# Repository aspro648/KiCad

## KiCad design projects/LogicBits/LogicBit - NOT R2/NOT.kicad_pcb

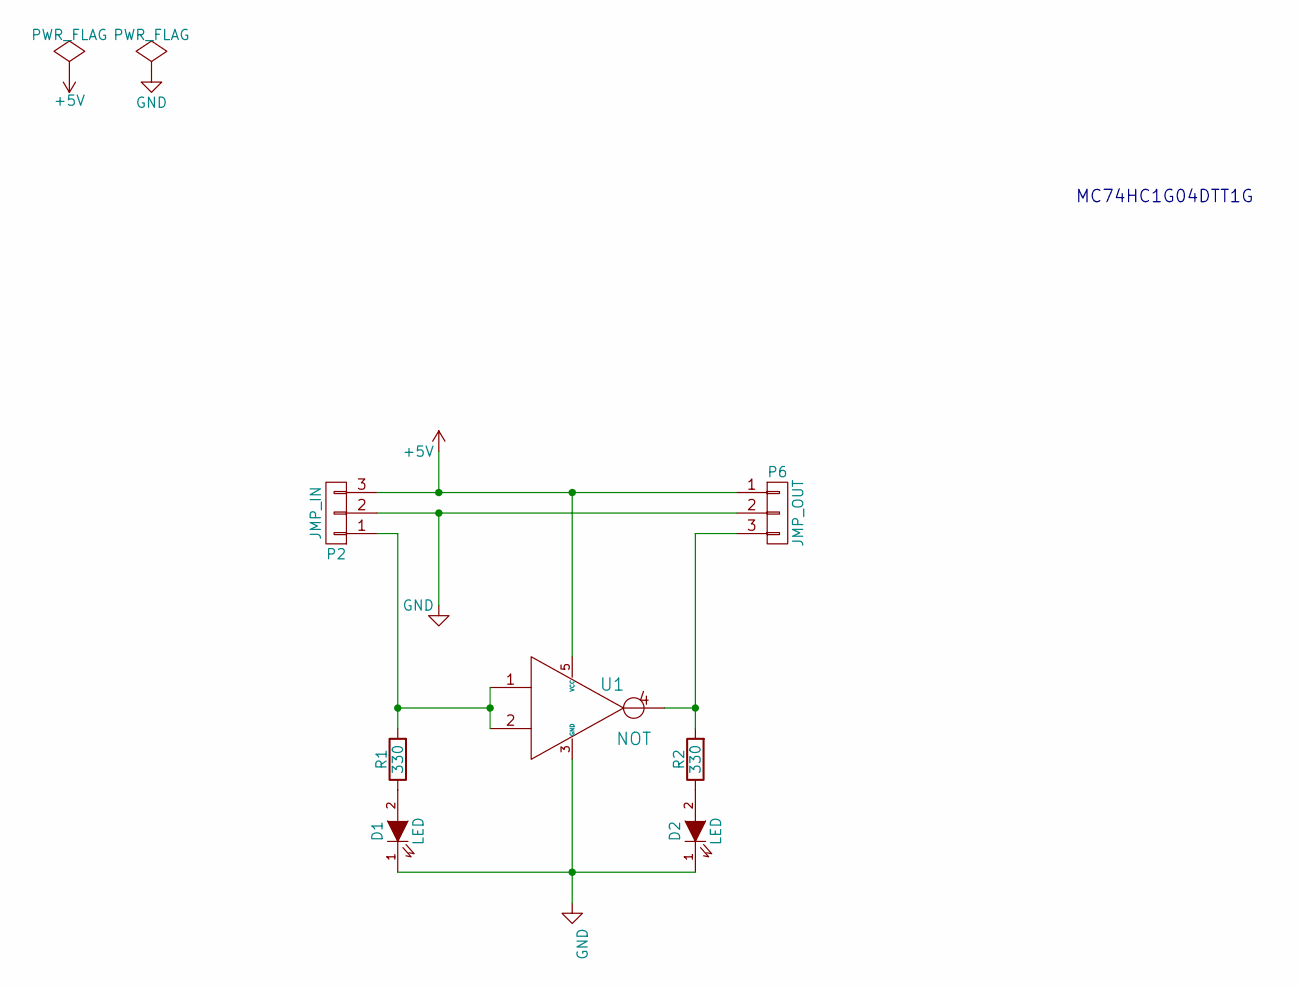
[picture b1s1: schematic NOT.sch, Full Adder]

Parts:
D1, D2: LED; LED-1206
P2: JMP_IN; Pin_Header_Angled_1x03
P6: JMP_OUT; Pin_Header_Angled_1x03
R1, R2: 330; R_1206
U1: NOT; SOT-23-5

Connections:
+5V: P2.3, P6.1, U1.5 (VCC)
GND: D1.1 (K), D2.1 (K), P2.2, P6.2, U1.3 (GND)
unnamed: D1.2 (A), R1.1
unnamed: D2.2 (A), R2.1
unnamed: P2.1, R1.2, U1.1, U1.2
unnamed: P6.3, R2.2, U1.4

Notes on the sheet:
MC74HC1G04DTT1G

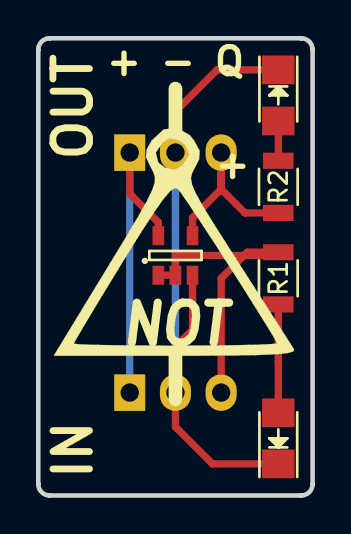
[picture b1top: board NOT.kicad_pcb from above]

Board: 2 copper layers, 15.2 x 25.4 mm, 9 parts (0 on the bottom side), 6 nets.

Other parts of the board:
Rec: myRec
VAL: MadeInOregonRev25

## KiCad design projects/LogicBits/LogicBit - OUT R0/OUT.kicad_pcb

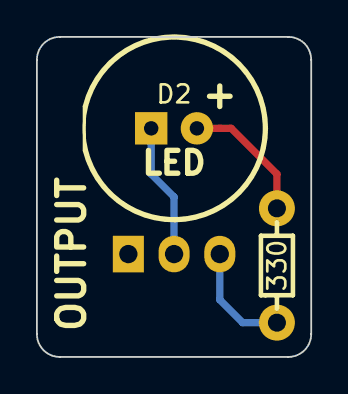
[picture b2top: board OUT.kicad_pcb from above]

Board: 2 copper layers, 15.2 x 17.8 mm, 4 parts (0 on the bottom side), 3 nets.

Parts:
D2: LED; LED-10MM
P2: JMP_IN; Pin_Header_Angled_1x03
R2: 330; Resistor_Horz
VAL: MadeInOregonRev25

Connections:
GND: D2.1, P2.2
unnamed: D2.2, R2.1
unnamed: P2.1, R2.2

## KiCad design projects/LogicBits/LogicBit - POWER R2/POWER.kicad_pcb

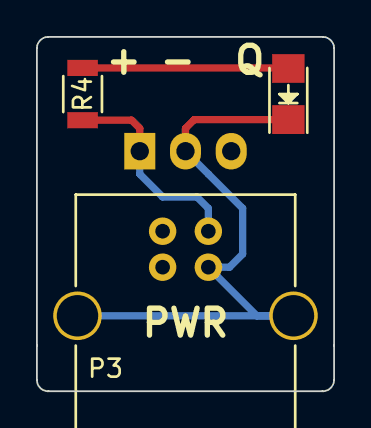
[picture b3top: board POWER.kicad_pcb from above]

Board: 2 copper layers, 16.5 x 19.7 mm, 5 parts (0 on the bottom side), 3 nets.

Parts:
D1: LED; LED-1206
P3: USB_B
P6: JMP_OUT; Pin_Header_Angled_1x03
R4: 330; R_1206
VAL: MadeInOregonRev25

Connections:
+5V: P3.1, P6.1, R4.1
GND: D1.1, P3.4, P3.5, P6.2
unnamed: D1.2, R4.2

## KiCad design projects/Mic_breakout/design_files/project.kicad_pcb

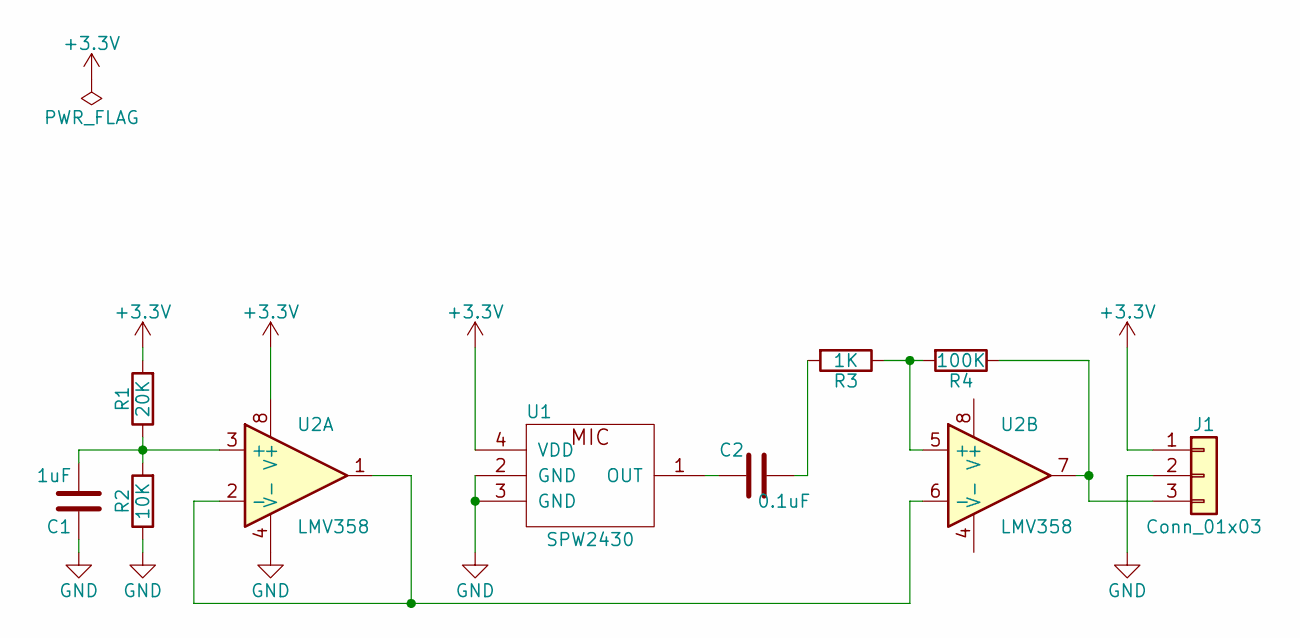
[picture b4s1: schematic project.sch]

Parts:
C1: 1uF; C_0805
C2: 0.1uF; C_0603
J1: Conn_01x03; Pin_Header_Straight_1x03_Pitch2.54mm
R1: 20K; R_0603
R2: 10K; R_0603
R3: 1K; R_0603
R4: 100K; R_0603
U1: SPW2430
U2: LMV358; TSSOP-8_3x3mm_Pitch0.65mm

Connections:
+3V3: J1.1, R1.2, U1.4 (VDD), U2.8 (V+)
GND: C1.1, J1.2, R2.1, U1.2 (GND), U1.3 (GND), U2.4 (V-)
unnamed: C1.2, R1.1, R2.2, U2.3 (+)
unnamed: C2.1, R3.2
unnamed: C2.2, U1.1 (OUT)
unnamed: J1.3, R4.1, U2.7
unnamed: R3.1, R4.2, U2.5 (+)
unnamed: U2.1, U2.2 (-), U2.6 (-)

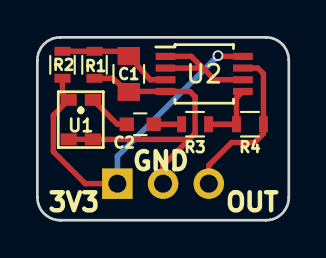
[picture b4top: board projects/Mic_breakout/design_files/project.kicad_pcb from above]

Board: 2 copper layers, 14.0 x 10.2 mm, 9 parts (0 on the bottom side), 8 nets.

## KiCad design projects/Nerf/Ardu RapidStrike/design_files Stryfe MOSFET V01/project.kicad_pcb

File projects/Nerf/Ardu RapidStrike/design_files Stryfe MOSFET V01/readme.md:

ArduStryfe MOSFET

Main Board
----------------
- 1 ea., 1N4001 1A Gen Purpose diode, https://www.digikey.com/short/p9ffm9
- 1 ea., MOSFET N-CH 30V 62A TO-220AB, Infineon IRLB8721PBF, https://www.digikey.com/short/p4fhcm
- 1 ea., PTC RESET FUSE 16V 900MA RADIAL, Littlefuse RUSBF090-2, https://www.digikey.com/short/p5vbvt
- 1 ea., PTC RESET FUSE 16V 2.5A RADIAL, Littlefuse RGEF250, https://www.digikey.com/short/pbfb9c

AA   3.5A @ 2.5s: RUSBF110 https://www.digikey.com/short/p5v5mz
LiPo 6.5A @ 2s:   RUSBF135 https://www.digikey.com/short/p5v5mc
MTRS  30A @ 3s: RGEF900  https://www.digikey.com/short/p5v54j

2.5A @ 2s: AHEF050: https://www.digikey.com/short/prwn0r
3.5A @ 2s: AHEF070: https://www.digikey.com/short/prwnv9

- 1 ea., 10K Resistors, 1/8W 5% generic, https://www.digikey.com/short/p4frj2 
- 1 ea., 2POS Picoblade vertical header, https://www.digikey.com/short/p9twrj
- 1 ea., 2POS PicoBlade housing, https://www.digikey.com/short/p4wz0d

- 2 ea., 12" PRE-CRIMP 1852 BLACK, https://www.digikey.com/short/pbfbnd

Revisions
----------------

License
----------------
[Attribution-ShareAlike 3.0 United States (CC BY-SA 3.0 US)](https://creativecommons.org/licenses/by-sa/3.0/us/)

You are free to:

- Share — copy and redistribute the material in any medium or format
- Adapt — remix, transform, and build upon the material

Under the following terms:

- Attribution — You must give appropriate credit, provide a link to the license, and indicate if changes were made. You may do so in any reasonable manner, but not in any way that suggests the licensor endorses you or your use.
- ShareAlike — If you remix, transform, or build upon the material, you must distribute your contributions under the same license as the original.

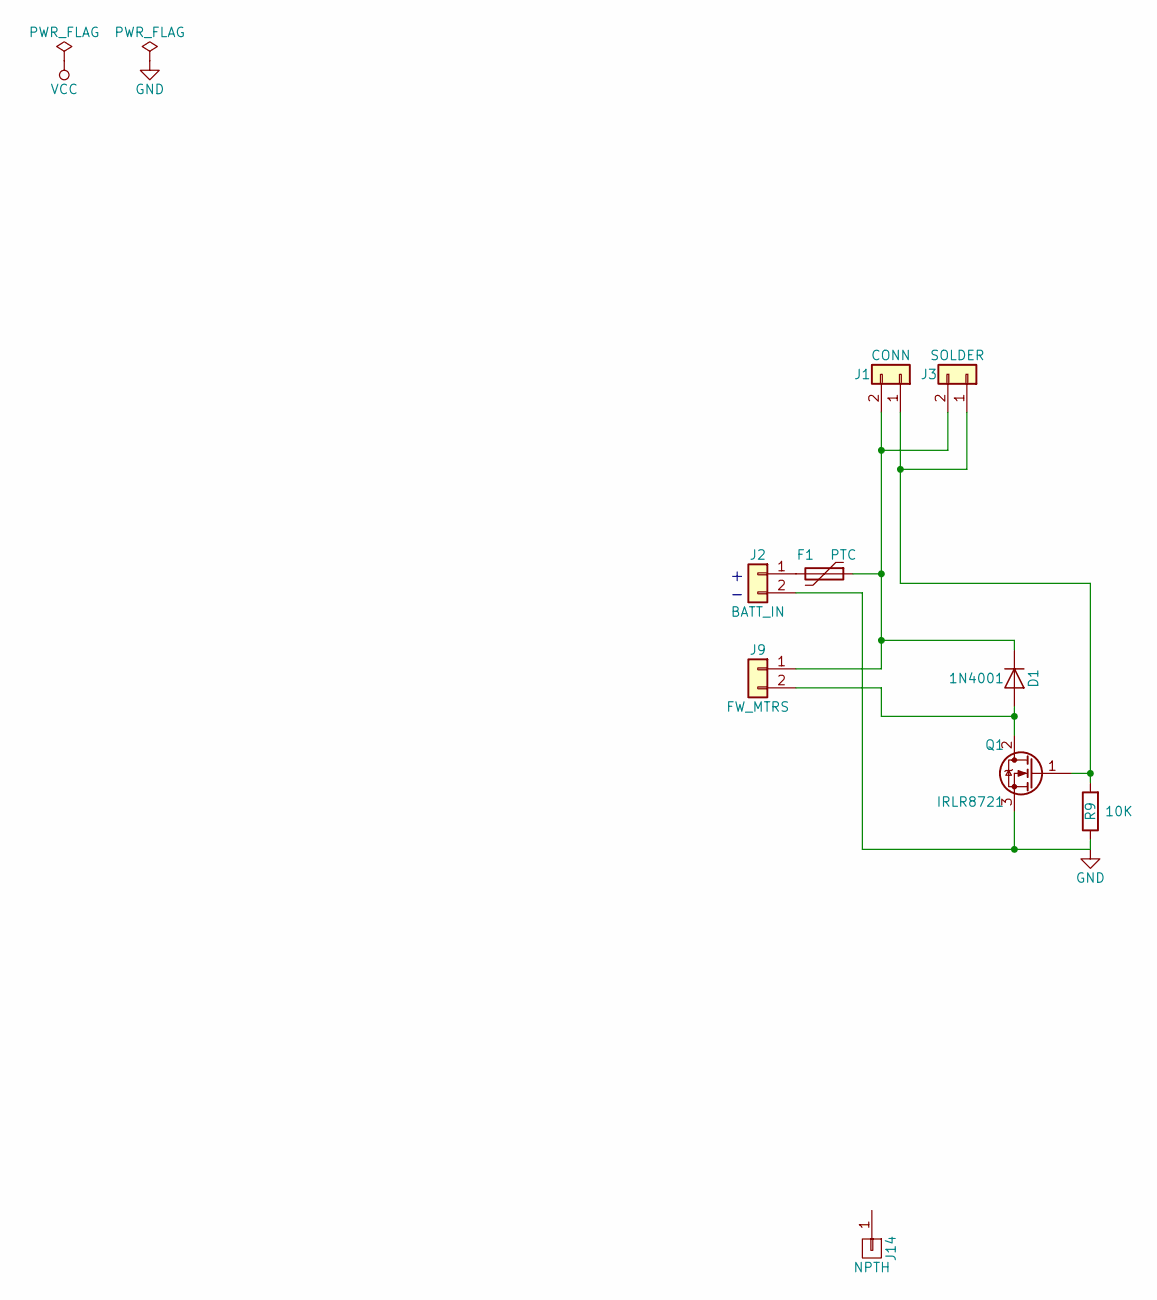
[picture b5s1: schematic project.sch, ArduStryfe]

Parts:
D1: 1N4001; D_DO-41
F1: PTC; Fuse_Littelfuse-LVR125
J1: CONN; Molex_PicoBlade_53047-0210_02x1.25mm_Straight
J2: BATT_IN; TerminalBlock_P3.50mm_Horizontal
J3: SOLDER; Pin_Header_Straight_1x02_Pitch2.00mm
J9: FW_MTRS; TerminalBlock_P3.50mm_Horizontal
J14: NPTH; SolderWirePad_single_2-5mmDrill
Q1: IRLR8721; TO-220-3_Horizontal
R9: 10K; R__P7mm

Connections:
GND: J2.2, Q1.3 (S), R9.1
unnamed: D1.1 (K), F1.1, J1.2, J3.2, J9.1
unnamed: D1.2 (A), J9.2, Q1.2 (D)
unnamed: F1.2, J2.1
unnamed: J1.1, J3.1, Q1.1 (G), R9.2

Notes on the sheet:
+ -

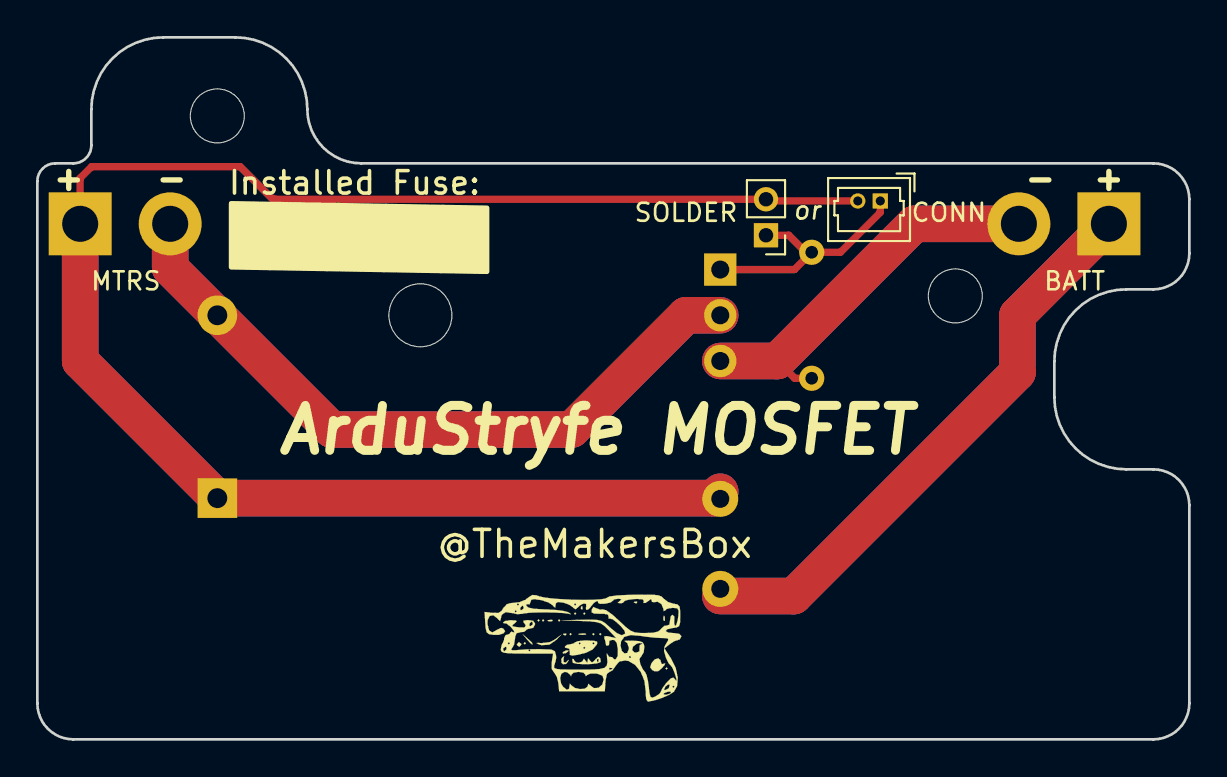
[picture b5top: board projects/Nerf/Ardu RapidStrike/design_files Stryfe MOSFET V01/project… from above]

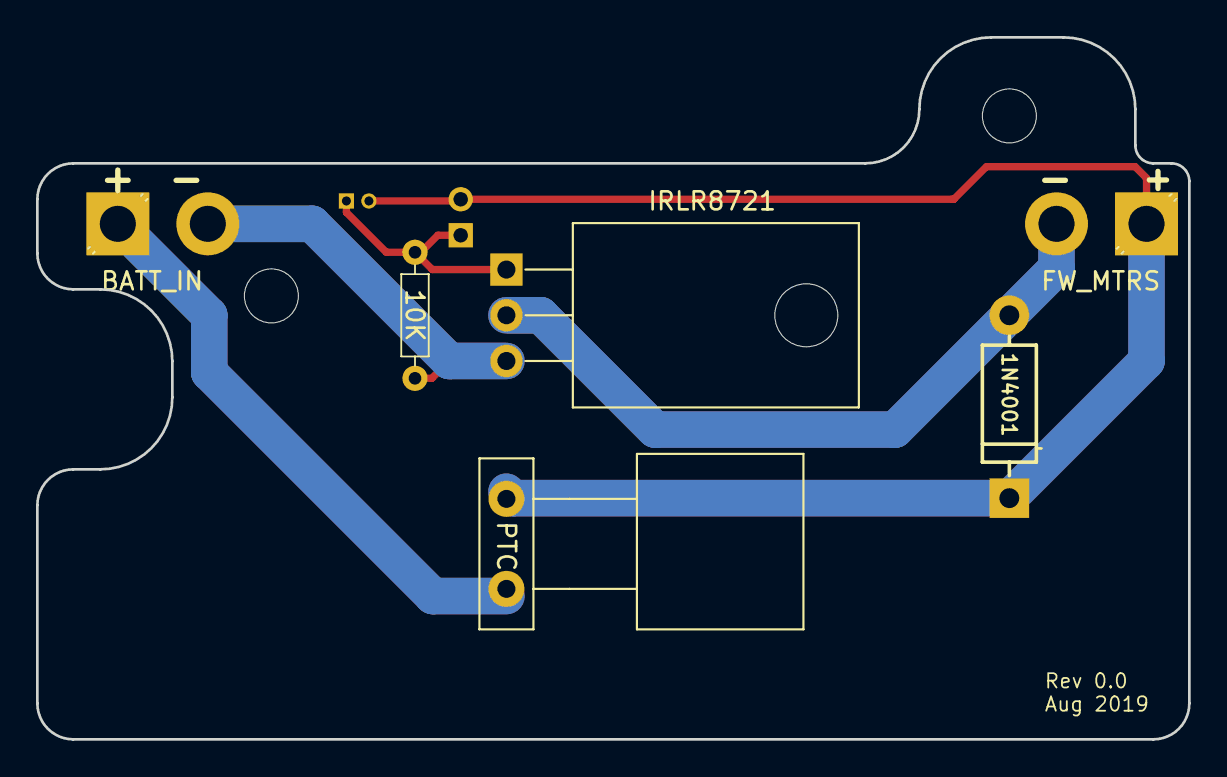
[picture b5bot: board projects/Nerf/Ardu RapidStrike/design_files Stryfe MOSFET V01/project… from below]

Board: 2 copper layers, 64.0 x 39.0 mm, 10 parts (6 on the bottom side), 5 nets.

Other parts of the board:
J14#2: NPTH; SolderWirePad_single_2-5mmDrill

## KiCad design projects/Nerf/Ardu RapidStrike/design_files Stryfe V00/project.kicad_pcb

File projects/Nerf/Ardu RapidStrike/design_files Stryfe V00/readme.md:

ArduStryfe 

Main Board
----------------
- 1 ea., Atmega328P-PU https://www.digikey.com/short/jn57wj
- 1 ea., CER RES 16.0000MHZ 30PF T/H, ECS ZTT-16.00MX, https://www.digikey.com/short/jn9pjv
- 1 ea., IC REG LINEAR 5V 250MA TO92-3, Microchip MCP1702-5002E/TO, https://www.digikey.com/short/pm2nmj
- 3 ea., Hall Effect Sensor, Diodes Incorporated AH9246-P-B, https://www.digikey.com/short/p4f5dw
- 1 ea., MOSFET N-CH 30V 58A DPAK, Infineon IRLR8729, https://www.digikey.com/short/pm0rdq
- 1 ea., CONN IC DIP SOCKET 16POS TIN, https://www.digikey.com/short/ph78mv
- 1 ea., PTC RESET FUSE 16V 5A RADIAL, https://www.digikey.com/short/ph7qmn
- 1 ea., 2N4401 NPN Transistor, https://www.digikey.com/short/pm0rwd
- 2 ea., CER 0.1UF 25V Y5V RADIAL 2.5mm lead spacing, generic, https://www.digikey.com/short/jn9pm2
- 2 ea., CER 1UF 25V X7R RADIAL 2.5 lead spacing, generic https://www.digikey.com/short/p4fr3w
- 1 ea., 0.96 Inch 128x64 I2C OLED, https://www.amazon.com/gp/product/B072Q2X2LL/

- 1 ea., 3mm LED red, https://www.digikey.com/short/pmwzdf
- 1 ea., 3mm IR LED, https://www.digikey.com/short/pmwzdq
- 1 ea., NPN photo transistor, https://www.digikey.com/short/pmwzdb

- 1 ea., 100 ohm resistor 1/8W 5% generic, https://www.digikey.com/short/pmwz22
- 5 ea., 1K ohm resistor 1/8W 5% generic, https://www.digikey.com/short/pmwzwq
- 4 ea., 10K Resistors, 1/8W 5% generic, https://www.digikey.com/short/p4frj2 

- 1 ea., 10K Resistors, 1/4W 1%, https://www.digikey.com/short/p4fr2q
- 2 ea., 100K Resistors, 1/8W 1%, https://www.digikey.com/short/ph7q59

- 1 ea., SWITCH TACTILE SPST-NO 0.05A 24V, https://www.digikey.com/short/p4w42v
- 1 ea., Piezo speaker, TDK PS1240P02CT3,  https://www.digikey.com/short/pmwzfc
- 1 ea., 28 Pin socket, On Shore ED281DT, https://www.digikey.com/short/jn5tz5

- 3 ea., 2POS Picoblade header, https://www.digikey.com/short/p4wz0w
- 3 ea., 2POS PicoBlade housing, https://www.digikey.com/short/p4wz0d

- 1 ea., 3POS Picoblade header, https://www.digikey.com/short/pmwzfb
- 1 ea., 3POS PicoBlade housing, https://www.digikey.com/short/pmwzf2

- 1 ea., 4POS Picoblade header, https://www.digikey.com/short/p4wz0m
- 2 ea., 4POS PicoBlade housing, https://www.digikey.com/short/p4wzd1

12" PRE-CRIMP 1853 RED, https://www.digikey.com/short/p4wzvf
12" PRE-CRIMP 1853 BLACK, https://www.digikey.com/short/p4wz1p
12" PRE-CRIMP 1853 BLUE, https://www.digikey.com/short/p4wz14
12" PRE-CRIMP 1853 ORANGE, https://www.digikey.com/short/p4wz1r
12" PRE-CRIMP 1853 GREEN, https://www.digikey.com/short/p4w4c4

16 AWG Silicone wire, https://www.amazon.com/BNTECHGO-Silicone-Flexible-Strands-Stranded/dp/B00TG1TRL2
18 AWG Silicone wire (7.5A, $0.40/ft), https://www.amazon.com/Silicone-Electrical-Conductor-Parallel-Flexible/dp/B07FMRDP87
16 AWG Silicone wire (12A, $0.70/ft), https://www.amazon.com/Silicone-Electrical-Conductor-Parallel-Flexible/dp/B07FMLVF84

XT60 connector male

Optional:
FTDI SERIAL TTL-232 USB CABLE, https://www.digikey.com/short/p4w47d
SPARKFUN FT231X BREAKOUT, https://www.digikey.com/short/p4w4qb

Motor Spec Sheet:
----------------
https://docs.google.com/spreadsheets/d/12gOU-GbuqdGVzpOjZJvQ_gq1Nmw63c_sd13Wt4bfn1E/edit#gid=0

Revisions
----------------

License
----------------
[Attribution-ShareAlike 3.0 United States (CC BY-SA 3.0 US)](https://creativecommons.org/licenses/by-sa/3.0/us/)

You are free to:

- Share — copy and redistribute the material in any medium or format
- Adapt — remix, transform, and build upon the material

Under the following terms:

- Attribution — You must give appropriate credit, provide a link to the license, and indicate if changes were made. You may do so in any reasonable manner, but not in any way that suggests the licensor endorses you or your use.
- ShareAlike — If you remix, transform, or build upon the material, you must distribute your contributions under the same license as the original.

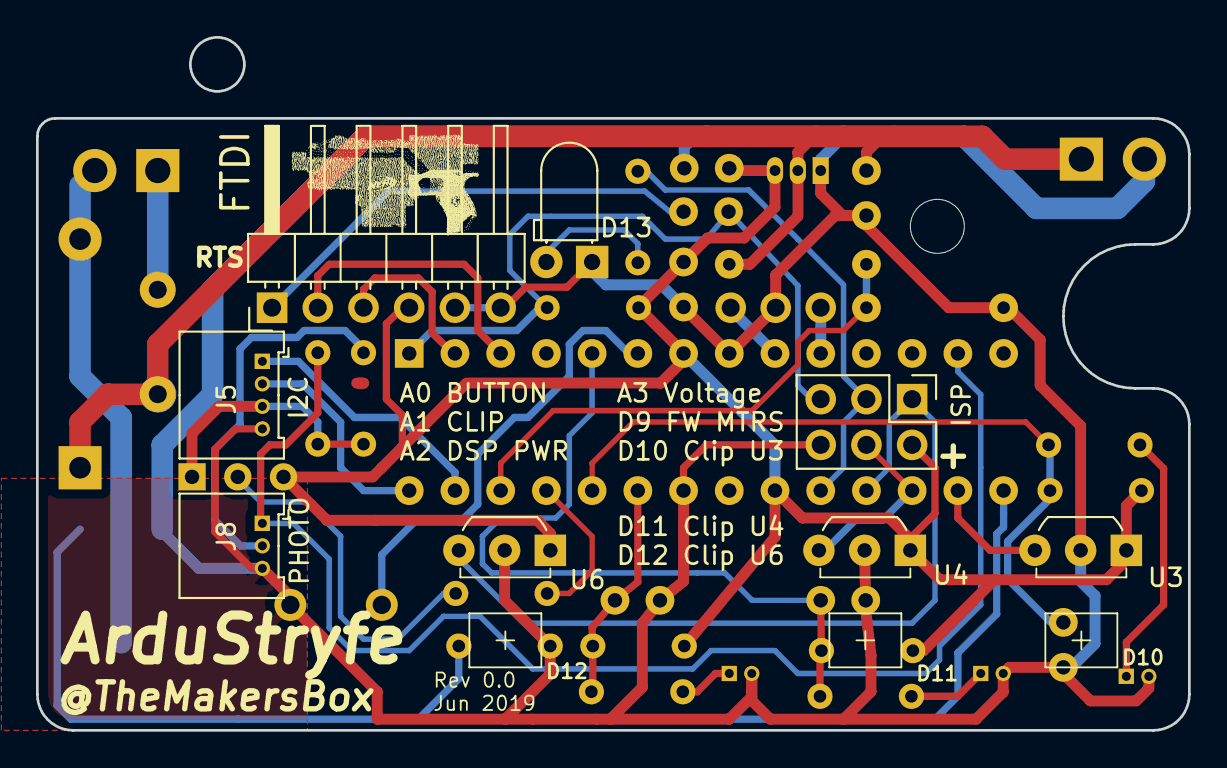
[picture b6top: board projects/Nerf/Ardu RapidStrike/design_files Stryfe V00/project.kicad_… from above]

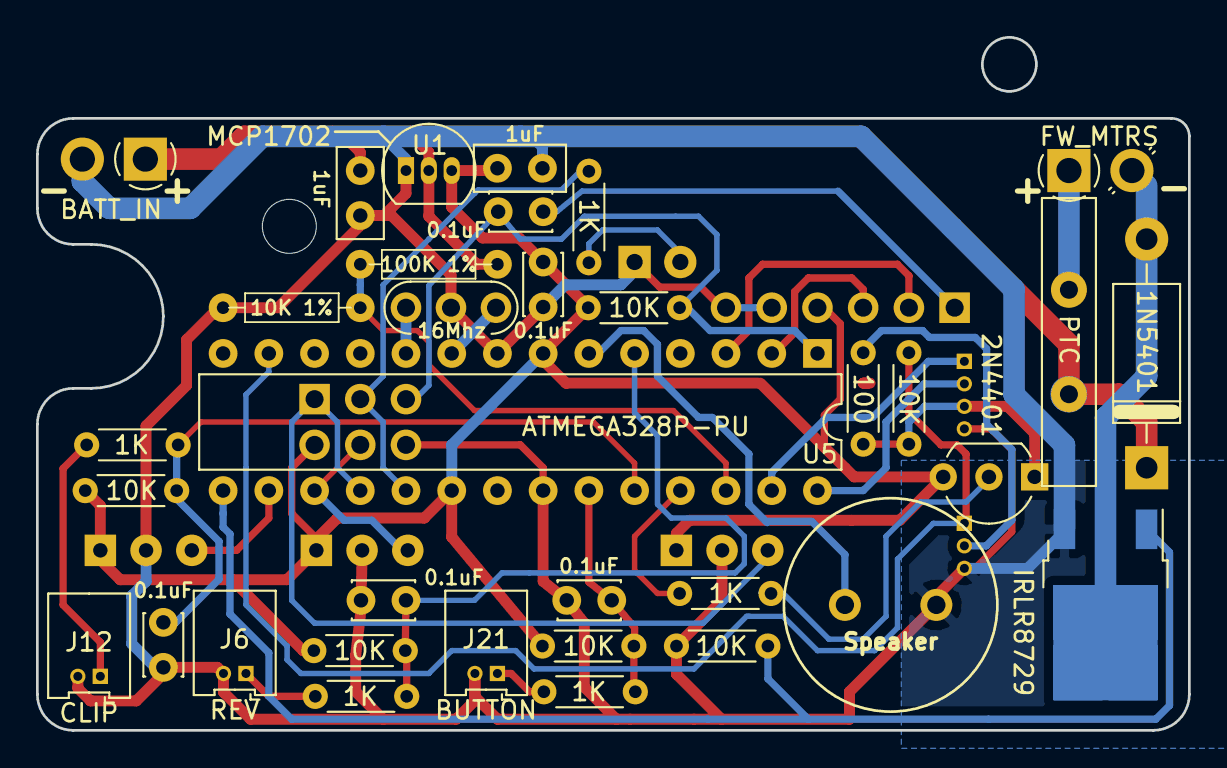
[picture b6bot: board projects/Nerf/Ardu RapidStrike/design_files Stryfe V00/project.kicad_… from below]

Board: 2 copper layers, 64.0 x 34.0 mm, 44 parts (34 on the bottom side), 32 nets.

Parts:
C1, C4: 1uF; C_Disc_D5.0mm_W2.5mm_P2.50mm
C5, C7, C8, C9, C10: 0.1uF; C_Disc_D3.4mm_W2.1mm_P2.50mm
CON1: ISP; Pin_Header_Straight_2x03_Pitch2.54mm
D1: 1N5401; D_DO-15_P12.70mm_Horizontal
D2: D13; LED_D3.0mm_Horizontal_O1.27mm_Z10.0mm
F1: PTC; Fuse_Littelfuse-LVR125
J2: BATT_IN; TerminalBlock_P3.50mm_Horizontal
J5: I2C; Molex_PicoBlade_53048-0410_04x1.25mm_Angled
J6: REV; Molex_PicoBlade_53048-0210_02x1.25mm_Angled
J7: FTDI; Pin_Header_Angled_1x06_Pitch2.54mm
J8: PHOTO; Molex_PicoBlade_53048-0310_03x1.25mm_Angled
J9: FW_MTRS; TerminalBlock_P3.50mm_Horizontal
J12: CLIP; Molex_PicoBlade_53048-0210_02x1.25mm_Angled
J14, J14#2: NPTH; SolderWirePad_single_2-5mmDrill
J21: BUTTON; Molex_PicoBlade_53048-0210_02x1.25mm_Angled
LS1: Speaker; SPEAKER
Q1: IRLR8729; TO-252-3_TabPin2
Q3: 2N4401; TO-92_Inline_Wide
R1, R2, R7, R11, R18: 1K; R__P5.08mm
R6, R9, R10, R17, R19, R20: 10K; R__P5.08mm
R8: 100K 1%; R_7.5mm
R12: 10K 1%; R_7.5mm
R21: 100; R__P5.08mm
U1: MCP1702; TO-92_Inline_Narrow_Oval
U3, U4, U6: HALL SENSOR; Hall_Sensor
U5: ATMEGA328P-PU; DIP-28_W7.62mm
Y1: 16Mhz; Resonator-3pin_w7.0mm_h2.5mm

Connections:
/0(Rx): J7.3, U5.2
/1(Tx): J7.2, U5.3
/3(**): C7.1, R6.1, R7.2, U5.5
/4: LS1.1, U5.6
/7: J8.1, R20.2, U5.13
/9(**): Q1.1, R9.2, U5.15
/10(SS): U3.3, U5.16
/11(MOSI): CON1.4, U4.3, U5.17
/12(MISO): CON1.1, U5.18, U6.3
/13(SCK): CON1.3, R2.1, U5.19
/#RTS: C9.1, J7.1
/A0: C10.1, R18.2, R19.1, U5.23
/A1: C8.1, R10.1, R11.2, U5.24
/A2: R1.2, U5.25
/A3: R8.1, R12.1, U5.26
/A4(SDA): J5.1, U5.27
/A5(SCL): J5.2, U5.28
/BATT: C1.1, D1.1, F1.1, J2.1, R8.2, U1.2
/Reset: C9.2, CON1.5, R17.1, U5.1
GND: C1.2, C4.2, C5.2, C7.2, C8.2, C10.2, CON1.6, D2.1, J2.2, J5.4, J6.2, J7.5, J7.6, J8.3, J12.2, J21.2, LS1.2, Q1.3, R9.1, R12.2, U1.1, U3.2, U4.2, U5.8, U5.22, U6.2, Y1.2
unnamed: D1.2, J9.2, Q1.2
unnamed: D2.2, R2.2
unnamed: F1.2, J9.1
unnamed: J5.3, Q3.1, R20.1, R21.1
unnamed: J6.1, R7.1
unnamed: J8.2, R21.2
unnamed: J12.1, R11.1
unnamed: J21.1, R18.1
unnamed: Q3.2, R1.1
unnamed: U5.9, Y1.3
unnamed: U5.10, Y1.1
VCC: C4.1, C5.1, CON1.2, J7.4, Q3.3, R6.2, R10.2, R17.2, R19.2, U1.3, U3.1, U4.1, U5.7, U5.20, U6.1
